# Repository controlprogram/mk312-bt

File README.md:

MK-312BT V1.2

Documentation at : http://tinyurl.com/mk312bt-info

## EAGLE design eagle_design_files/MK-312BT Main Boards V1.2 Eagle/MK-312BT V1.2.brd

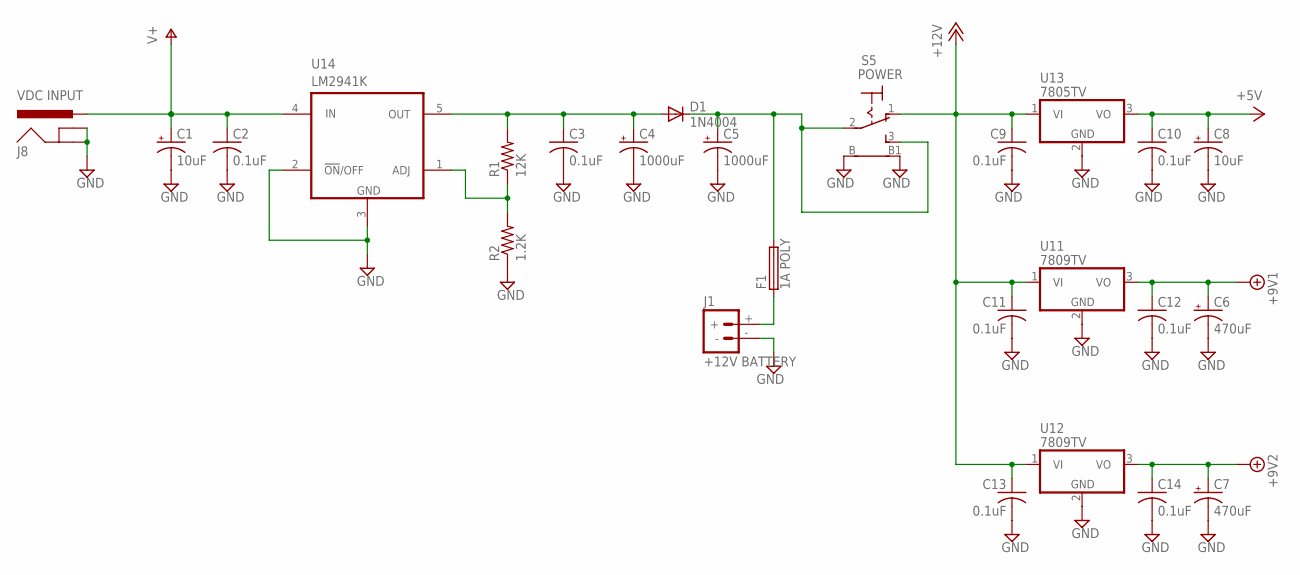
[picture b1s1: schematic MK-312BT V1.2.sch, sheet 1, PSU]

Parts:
C1, C8: 10uF; E2,5-7
C2, C3, C9, C10, C11, C12, C13, C14: 0.1uF; C025-024X044
C4, C5: 1000uF; E5-10,5
C6, C7: 470uF; E3,5-8
D1: 1N4004; DO41-10
F1: 1A POLY; LITTLEFUSE
J1: +12V BATTERY; DEANS
J8: VDC INPUT; POWER_JACK_SLOT
R1: 12K; 0207/10
R2: 1.2K; 0207/10
S5: POWER; LPV-1
U11, U12: 7809TV; TO220V
U13: 7805TV; TO220V
U14: LM2941K; TO220-5KC

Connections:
+5V: C8.+, C10.1, U13.3 (VO); also elsewhere on the board
+8V: C6.+, C12.1, U11.3 (VO); also elsewhere on the board
+9V: C7.+, C14.1, U12.3 (VO); also elsewhere on the board
+12V: C9.1, C11.1, C13.1, S5.1 (O), U11.1 (VI), U12.1 (VI), U13.1 (VI); also elsewhere on the board
GND: C1.-, C2.2, C3.2, C4.-, C5.-, C6.-, C7.-, C8.-, C9.2, C10.2, C11.2, C12.2, C13.2, C14.2, J1.-, J8.GND@1 (GNDBREAK), J8.GND@2 (GND), R2.1, S5.B, S5.B1, U11.2 (GND), U12.2 (GND), U13.2 (GND), U14.2 (!ON!/OFF), U14.3 (GND); also elsewhere on the board
unnamed: F1.1, J1.+
unnamed: R1.1, R2.2, U14.1 (ADJ)
unnamed: C3.1, C4.+, D1.A, R1.2, U14.5 (OUT)
unnamed: C5.+, D1.C, F1.2, S5.2, S5.3 (S)
V+: C1.+, C2.1, J8.PWR, U14.4 (IN); also elsewhere on the board

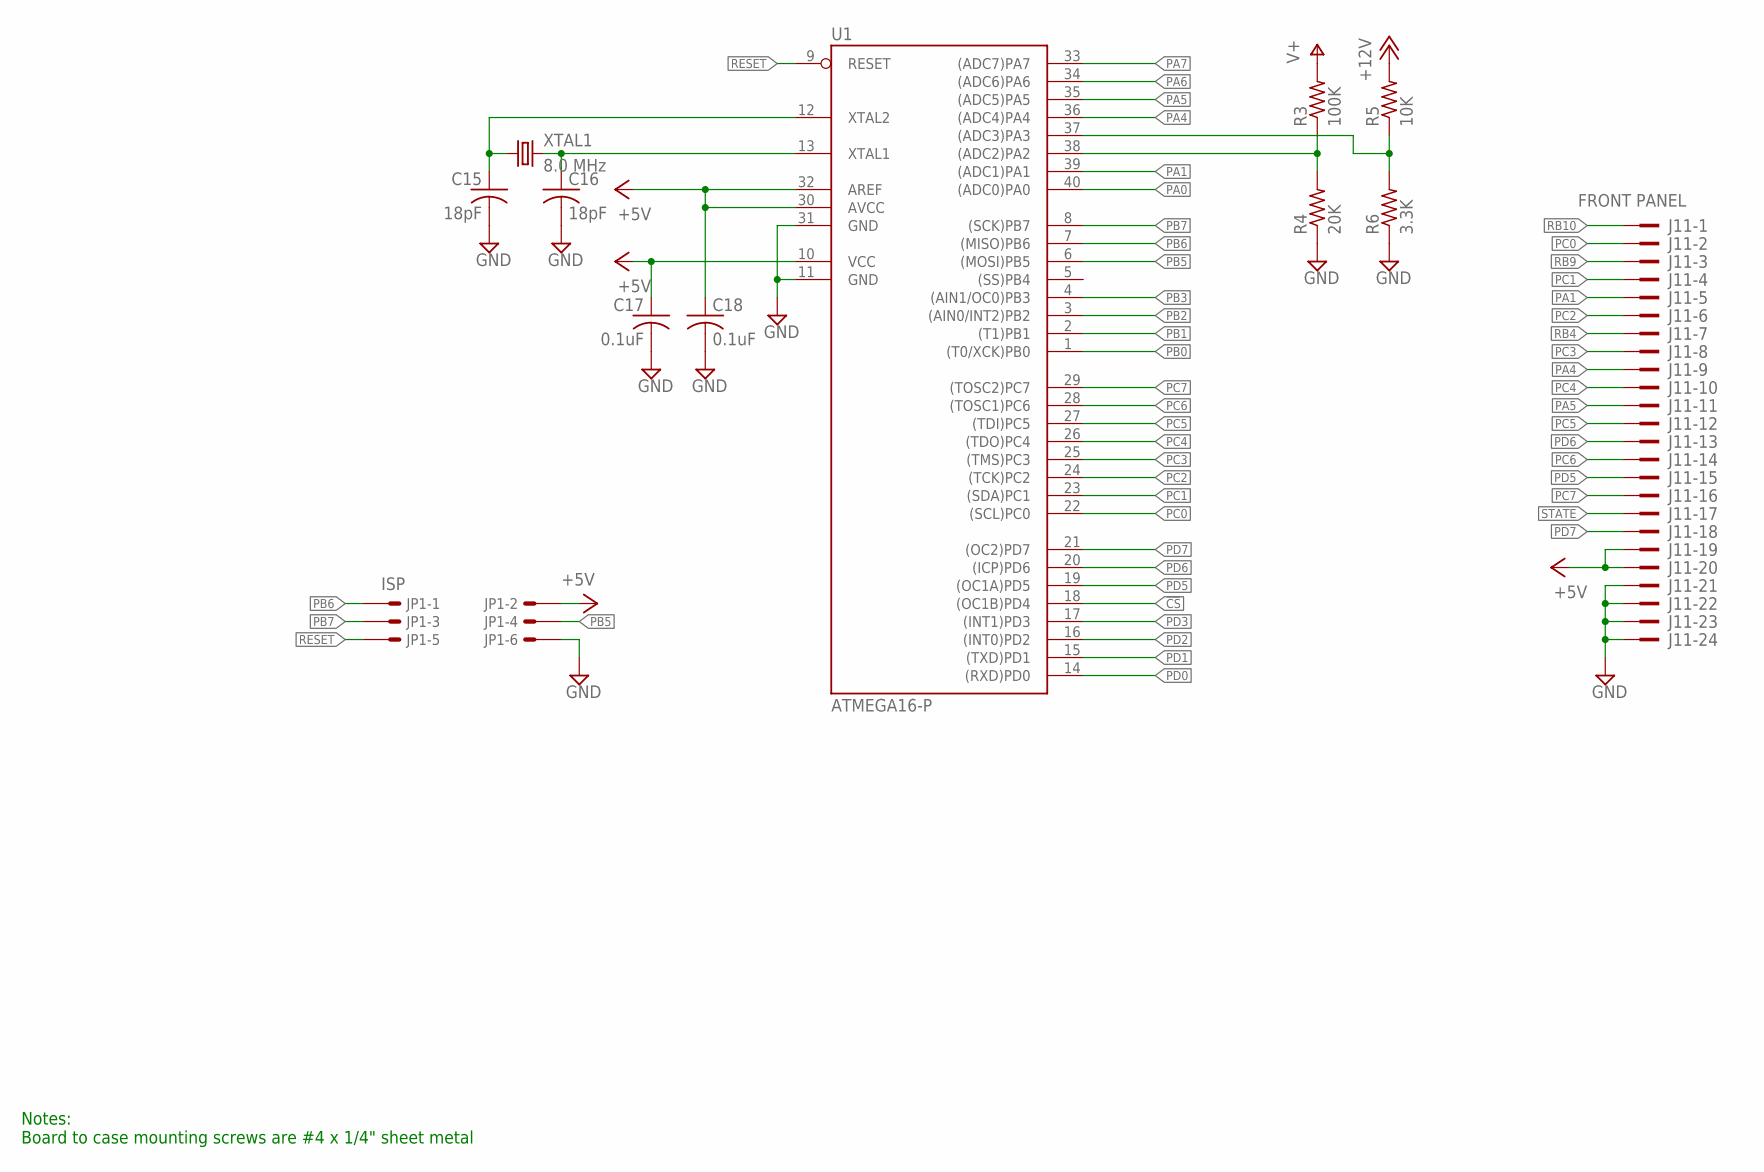
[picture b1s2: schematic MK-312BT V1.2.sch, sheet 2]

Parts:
C15, C16: 18pF; C025-024X044
C17, C18: 0.1uF; C025-024X044
J11: FRONT PANEL; PAK100/2500-24
JP1: ISP; 057-006-1
R3: 100K; 0207/10
R4: 20K; 0207/10
R5: 10K; 0207/10
R6: 3.3K; 0207/10
U1: ATMEGA16-P; DIL40
XTAL1: 8.0 MHz; HC49/S

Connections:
!CS: U1.18 ((OC1B)PD4); also elsewhere on the board
+5V: C17.1, C18.1, J11.19, J11.20, JP1.2, U1.10 (VCC), U1.30 (AVCC), U1.32 (AREF); also elsewhere on the board
+12V: R5.2; also elsewhere on the board
GND: C15.2, C16.2, C17.2, C18.2, J11.21, J11.22, J11.23, J11.24, JP1.6, R4.1, R6.1, U1.11 (GND), U1.31 (GND); also elsewhere on the board
unnamed: R5.1, R6.2, U1.37 ((ADC3)PA3)
unnamed: R3.1, R4.2, U1.38 ((ADC2)PA2)
unnamed: C16.1, U1.13 (XTAL1), XTAL1.2
unnamed: C15.1, U1.12 (XTAL2), XTAL1.1
PA0: U1.40 ((ADC0)PA0); also elsewhere on the board
PA1: J11.5, U1.39 ((ADC1)PA1); also elsewhere on the board
PA4: J11.9, U1.36 ((ADC4)PA4)
PA5: J11.11, U1.35 ((ADC5)PA5)
PA6: U1.34 ((ADC6)PA6); also elsewhere on the board
PA7: U1.33 ((ADC7)PA7); also elsewhere on the board
PB0: U1.1 ((T0/XCK)PB0); also elsewhere on the board
PB1: U1.2 ((T1)PB1); also elsewhere on the board
PB2: U1.3 ((AIN0/INT2)PB2); also elsewhere on the board
PB3: U1.4 ((AIN1/OC0)PB3); also elsewhere on the board
PB5: JP1.4, U1.6 ((MOSI)PB5); also elsewhere on the board
PB6: JP1.1, U1.7 ((MISO)PB6)
PB7: JP1.3, U1.8 ((SCK)PB7); also elsewhere on the board
PC0: J11.2, U1.22 ((SCL)PC0); also elsewhere on the board
PC1: J11.4, U1.23 ((SDA)PC1); also elsewhere on the board
PC2: J11.6, U1.24 ((TCK)PC2); also elsewhere on the board
PC3: J11.8, U1.25 ((TMS)PC3); also elsewhere on the board
PC4: J11.10, U1.26 ((TDO)PC4); also elsewhere on the board
PC5: J11.12, U1.27 ((TDI)PC5); also elsewhere on the board
PC6: J11.14, U1.28 ((TOSC1)PC6); also elsewhere on the board
PC7: J11.16, U1.29 ((TOSC2)PC7); also elsewhere on the board
PD0: U1.14 ((RXD)PD0); also elsewhere on the board
PD1: U1.15 ((TXD)PD1); also elsewhere on the board
PD2: U1.16 ((INT0)PD2); also elsewhere on the board
PD3: U1.17 ((INT1)PD3); also elsewhere on the board
PD5: J11.15, U1.19 ((OC1A)PD5); also elsewhere on the board
PD6: J11.13, U1.20 ((ICP)PD6); also elsewhere on the board
PD7: J11.18, U1.21 ((OC2)PD7); also elsewhere on the board
RB4: J11.7; also elsewhere on the board
RB9: J11.3; also elsewhere on the board
RB10: J11.1; also elsewhere on the board
RESET: JP1.5, U1.9 (RESET)
STATE: J11.17; also elsewhere on the board
V+: R3.2; also elsewhere on the board

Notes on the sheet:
Notes: Board to case mounting screws are #4 x 1/4" sheet metal

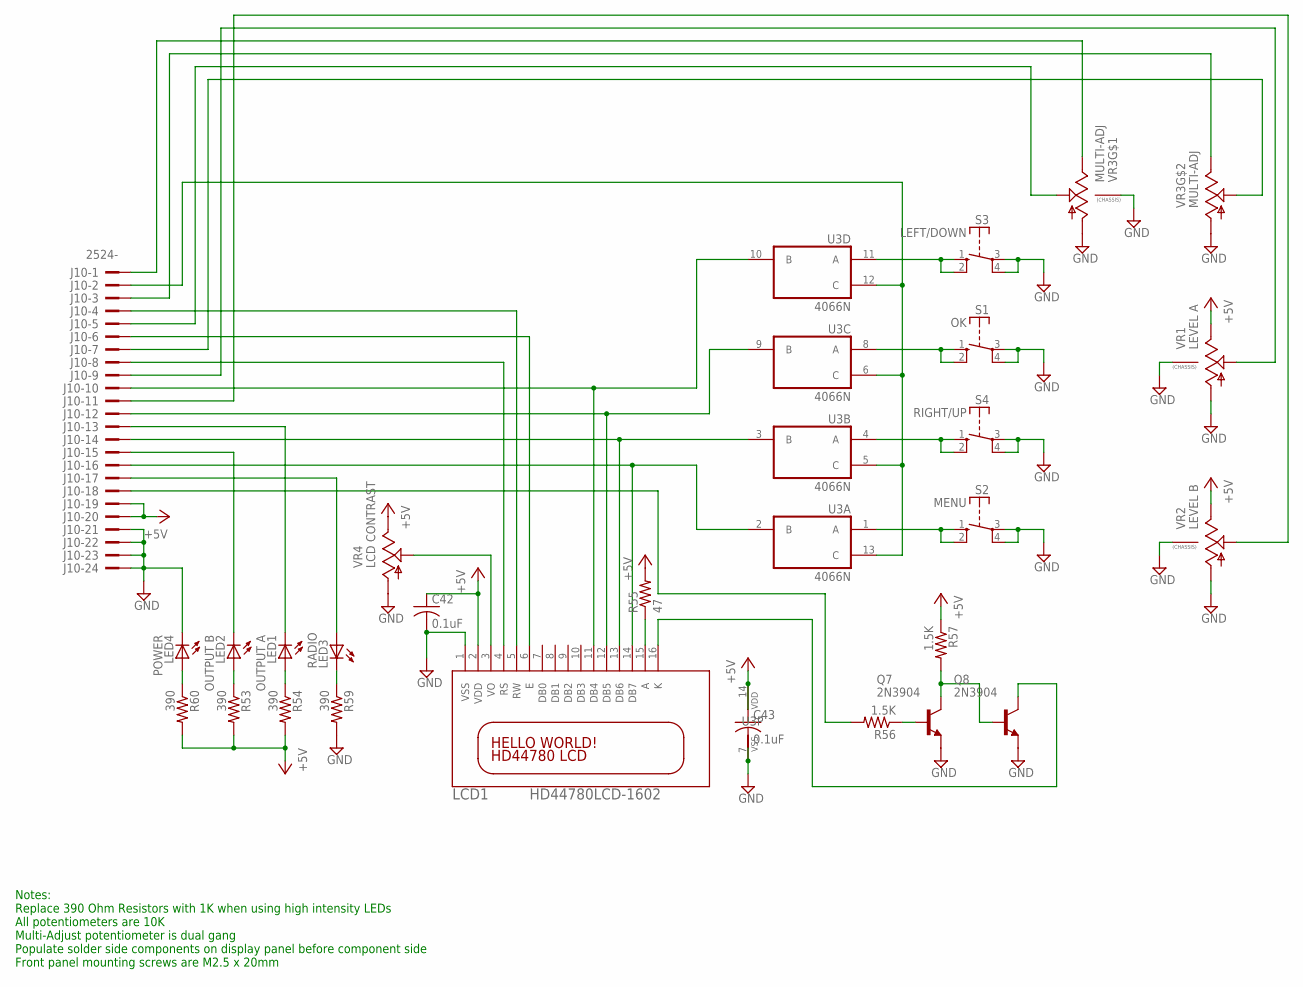
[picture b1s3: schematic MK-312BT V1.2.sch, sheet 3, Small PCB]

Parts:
C42, C43: 0.1uF; C025-024X044
J10: 2524-; PAK100/2500-24
LCD1: HD44780LCD-1602; LCD1602
LED1: OUTPUT A; LED5MM
LED2: OUTPUT B; LED5MM
LED3: RADIO; LED5MM
LED4: POWER; LED5MM
Q7, Q8: 2N3904; TO92
R53, R54, R59, R60: 390; 0207/10
R55: 47; 0207/10
R56, R57: 1.5K; 0207/10
S1: OK; DTE6K
S2: MENU; DTE6K
S3: LEFT/DOWN; DTE6K
S4: RIGHT/UP; DTE6K
U3: 4066N; DIL14
VR1: LEVEL A; 9MM_SNAP-IN_POT
VR2: LEVEL B; 9MM_SNAP-IN_POT
VR3: MULTI-ADJ; DUAL_9MM_SNAP-IN_POT
VR4: LCD CONTRAST; B25P

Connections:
+5V: C42.1, C43.1, J10.19, J10.20, LCD1.2 (VDD), R53.2, R54.2, R55.2, R57.1, R60.2, U3.14 (VDD), VR1.3 (E), VR2.3 (E), VR4.E; also elsewhere on the board
GND: C42.2, C43.2, J10.21, J10.22, J10.23, J10.24, LCD1.1 (VSS), LED4.K (C), Q7.3 (E), Q8.3 (E), R59.2, S1.3, S1.4, S2.3, S2.4, S3.3, S3.4, S4.3, S4.4, U3.7 (VSS), VR1.1 (A), VR1.CHASSIS2, VR2.1 (A), VR2.CHASSIS2, VR3.1 (A), VR3.1B (A), VR3.CHASSIS1, VR3.CHASSIS2, VR4.A; also elsewhere on the board
unnamed: J10.7, VR3.2B (S)
unnamed: S1.1 (S), S1.2 (S), U3.8 (A)
unnamed: S3.1 (S), S3.2 (S), U3.11 (A)
unnamed: S4.1 (S), S4.2 (S), U3.4 (A)
unnamed: J10.3, VR3.3B (E)
unnamed: J10.9, VR1.2 (S)
unnamed: J10.11, VR2.2 (S)
unnamed: J10.1, VR3.3 (E)
unnamed: J10.5, VR3.2 (S)
unnamed: LED2.A, R53.1
unnamed: LED1.A, R54.1
unnamed: LCD1.3 (VO), VR4.S
unnamed: LCD1.15 (A), R55.1
unnamed: LED3.K (C), R59.1
unnamed: S2.1 (S), S2.2 (S), U3.1 (A)
unnamed: LED4.A, R60.1
unnamed: Q7.2 (B), R56.1
unnamed: Q7.1 (C), Q8.2 (B), R57.2
unnamed: LCD1.16 (K), Q8.1 (C)
unnamed: J10.17, LED3.A
PC0: J10.2, U3.5 (C), U3.6 (C), U3.12 (C), U3.13 (C); also elsewhere on the board
PC1: J10.4, LCD1.5 (RW); also elsewhere on the board
PC2: J10.6, LCD1.6 (E); also elsewhere on the board
PC3: J10.8, LCD1.4 (RS); also elsewhere on the board
PC4: J10.10, LCD1.11 (DB4), U3.10 (B); also elsewhere on the board
PC5: J10.12, LCD1.12 (DB5), U3.9 (B); also elsewhere on the board
PC6: J10.14, LCD1.13 (DB6), U3.3 (B); also elsewhere on the board
PC7: J10.16, LCD1.14 (DB7), U3.2 (B); also elsewhere on the board
PD5: J10.15, LED2.K (C); also elsewhere on the board
PD6: J10.13, LED1.K (C); also elsewhere on the board
PD7: J10.18, R56.2; also elsewhere on the board

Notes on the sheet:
Notes: Replace 390 Ohm Resistors with 1K when using high intensity LEDs All potentiometers are 10K Multi-Adjust potentiometer is dual gang Populate solder side components on display panel before component side Front panel mounting screws are M2.5 x 20mm

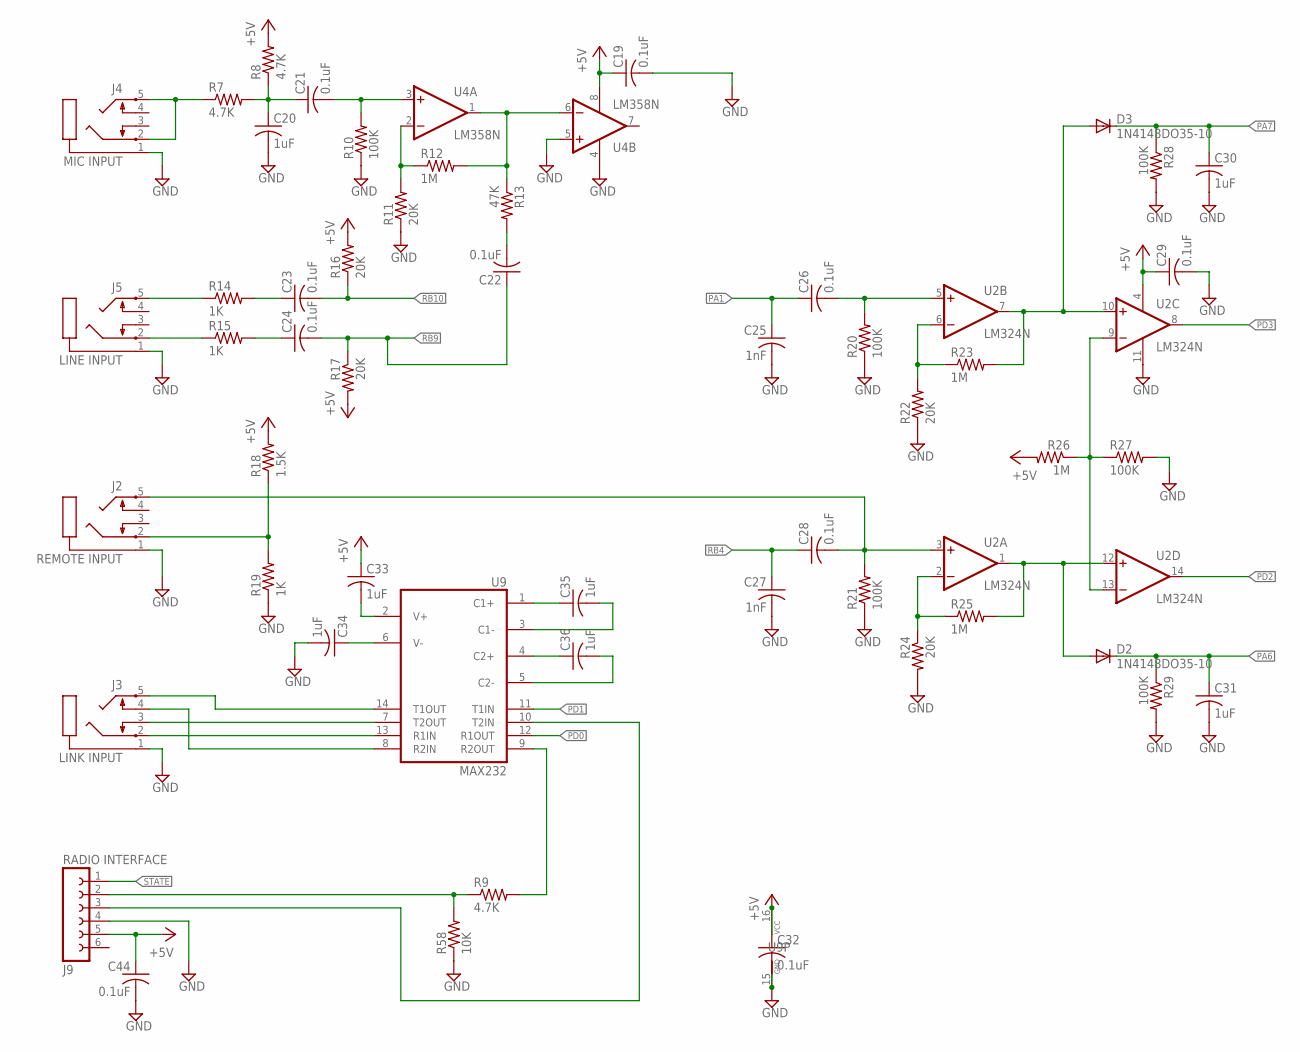
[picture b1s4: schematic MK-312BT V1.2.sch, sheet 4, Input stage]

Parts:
C19, C21, C22, C23, C24, C26, C28, C29, C32, C44: 0.1uF; C025-024X044
C20, C30, C31, C33, C34, C35, C36: 1uF; C025-024X044
C25, C27: 1nF; C025-024X044
D2, D3: 1N4148DO35-10; DO35-10
J2: REMOTE INPUT; STX3100
J3: LINK INPUT; STX3100
J4: MIC INPUT; STX3100
J5: LINE INPUT; STX3100
J9: RADIO INTERFACE; FE06
R7, R8, R9: 4.7K; 0207/10
R10, R20, R21, R27, R28, R29: 100K; 0207/10
R11, R16, R17, R22, R24: 20K; 0207/10
R12, R23, R25, R26: 1M; 0207/10
R13: 47K; 0207/10
R14, R15, R19: 1K; 0207/10
R18: 1.5K; 0207/10
R58: 10K; 0207/10
U2: LM324N; DIL14
U4: LM358N; DIL08
U9: MAX232; DIL16

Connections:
+5V: C19.1, C29.1, C32.1, C33.1, C44.1, J9.5, R8.2, R16.2, R17.2, R18.2, R26.2, U2.4 (V+), U4.8 (V+), U9.16 (VCC); also elsewhere on the board
GND: C19.2, C20.2, C25.2, C27.2, C29.2, C30.2, C31.2, C32.2, C34.2, C44.2, J2.1, J3.1, J4.1, J5.1, J9.4, R10.1, R11.1, R19.1, R20.1, R21.1, R22.1, R24.2, R27.2, R28.2, R29.2, R58.1, U2.11 (V-), U4.4 (V-), U4.5 (+IN), U9.15 (GND); also elsewhere on the board
unnamed: C28.2, J2.5, R21.2, U2.3 (+IN)
unnamed: R9.2, U9.9 (R2OUT)
unnamed: J3.5, U9.14 (T1OUT)
unnamed: J3.2, U9.13 (R1IN)
unnamed: C35.1, U9.1 (C1+)
unnamed: R24.1, R25.1, U2.2 (-IN)
unnamed: D2.A, R25.2, U2.1 (OUT), U2.12 (+IN)
unnamed: J5.2, R15.1
unnamed: J5.5, R14.1
unnamed: C23.1, R14.2
unnamed: J2.2, R18.1, R19.2
unnamed: R22.2, R23.1, U2.6 (-IN)
unnamed: C35.2, U9.3 (C1-)
unnamed: R26.1, R27.1, U2.9 (-IN), U2.13 (-IN)
unnamed: C26.2, R20.2, U2.5 (+IN)
unnamed: C24.1, R15.2
unnamed: C36.2, U9.5 (C2-)
unnamed: C36.1, U9.4 (C2+)
unnamed: J9.2, R9.1, R58.2
unnamed: D3.A, R23.2, U2.7 (OUT), U2.10 (+IN)
unnamed: C34.1, U9.6 (V-)
unnamed: J4.2, J4.5, R7.1
unnamed: C20.1, C21.1, R7.2, R8.1
unnamed: C21.2, R10.2, U4.3 (+IN)
unnamed: R11.2, R12.1, U4.2 (-IN)
unnamed: R12.2, R13.1, U4.1 (OUT), U4.6 (-IN)
unnamed: C22.2, R13.2
unnamed: C33.2, U9.2 (V+)
unnamed: J3.4, U9.8 (R2IN)
unnamed: J3.3, U9.7 (T2OUT)
unnamed: J9.3, U9.10 (T2IN)
PA1: C25.1, C26.1; also elsewhere on the board
PA6: C31.1, D2.C, R29.1; also elsewhere on the board
PA7: C30.1, D3.C, R28.1; also elsewhere on the board
PD0: U9.12 (R1OUT); also elsewhere on the board
PD1: U9.11 (T1IN); also elsewhere on the board
PD2: U2.14 (OUT); also elsewhere on the board
PD3: U2.8 (OUT); also elsewhere on the board
RB4: C27.1, C28.1; also elsewhere on the board
RB9: C22.1, C24.2, R17.1; also elsewhere on the board
RB10: C23.2, R16.1; also elsewhere on the board
STATE: J9.1; also elsewhere on the board

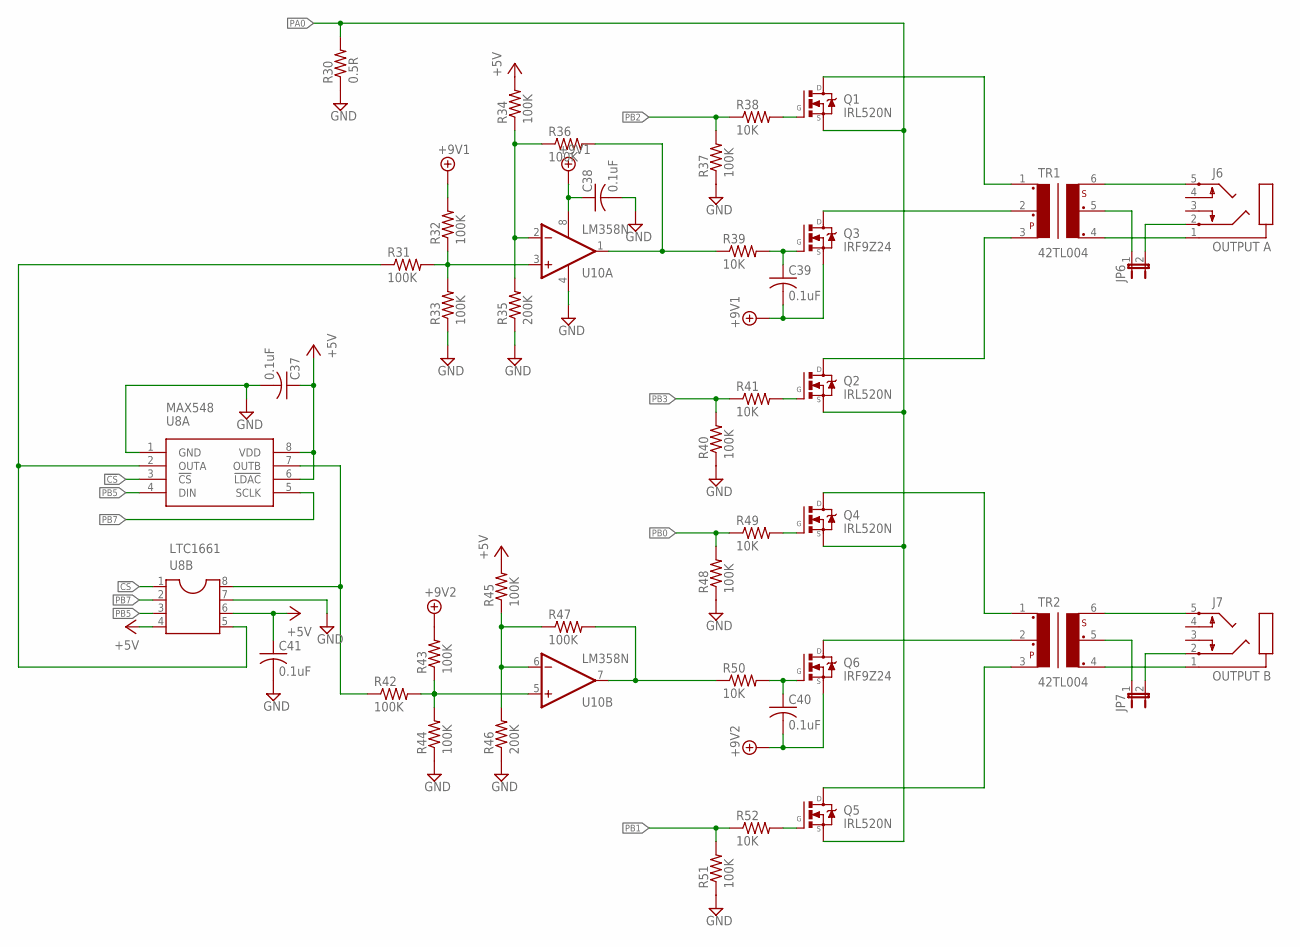
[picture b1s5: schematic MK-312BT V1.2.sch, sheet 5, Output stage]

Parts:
C37, C38, C39, C40, C41: 0.1uF; C025-024X044
J6: OUTPUT A; STX3100
J7: OUTPUT B; STX3100
JP6, JP7: JP1E; JP1
Q1, Q2, Q4, Q5: IRL520N; TO220V
Q3, Q6: IRF9Z24; TO220V
R30: 0.5R; 0309/12
R31, R32, R33, R34, R36, R37, R40, R42, R43, R44, R45, R47, R48, R51: 100K; 0207/10
R35, R46: 200K; 0207/10
R38, R39, R41, R49, R50, R52: 10K; 0207/10
TR1, TR2: 42TL004; 42TL
U8A: MAX548; DIL08
U8B: LTC1661; SOCKET-08
U10: LM358N; DIL08

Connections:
!CS: U8A.3 (!CS), U8B.1; also elsewhere on the board
+5V: C37.1, C41.1, R34.2, R45.2, U8A.6 (!LDAC), U8A.8 (VDD), U8B.4, U8B.6; also elsewhere on the board
+8V: C38.1, C39.2, Q3.3 (S), R32.2, U10.8 (V+); also elsewhere on the board
+9V: C40.2, Q6.3 (S), R43.2; also elsewhere on the board
GND: C37.2, C38.2, C41.2, R30.1, R33.1, R35.1, R37.1, R40.1, R44.1, R46.1, R48.1, R51.1, U8A.1 (GND), U8B.7, U10.4 (V-); also elsewhere on the board
unnamed: J6.1, TR1.4
unnamed: JP7.1, TR2.5
unnamed: J6.5, TR1.6
unnamed: Q1.1 (G), R38.2
unnamed: Q2.1 (G), R41.2
unnamed: J7.2, JP7.2
unnamed: C39.1, Q3.1 (G), R39.2
unnamed: R31.2, R32.1, R33.2, U10.3 (+IN)
unnamed: Q4.1 (G), R49.2
unnamed: Q5.1 (G), R52.2
unnamed: C40.1, Q6.1 (G), R50.2
unnamed: R42.2, R43.1, R44.2, U10.5 (+IN)
unnamed: Q1.2 (D), TR1.1
unnamed: Q3.2 (D), TR1.2
unnamed: Q4.2 (D), TR2.1
unnamed: Q6.2 (D), TR2.2
unnamed: Q5.2 (D), TR2.3
unnamed: Q2.2 (D), TR1.3
unnamed: R34.1, R35.2, R36.1, U10.2 (-IN)
unnamed: R45.1, R46.2, R47.1, U10.6 (-IN)
unnamed: R31.1, U8A.2 (OUTA), U8B.5
unnamed: J6.2, JP6.2
unnamed: J7.5, TR2.6
unnamed: J7.1, TR2.4
unnamed: JP6.1, TR1.5
unnamed: R42.1, U8A.7 (OUTB), U8B.8
PA0: Q1.3 (S), Q2.3 (S), Q4.3 (S), Q5.3 (S), R30.2; also elsewhere on the board
PB0: R48.2, R49.1; also elsewhere on the board
PB1: R51.2, R52.1; also elsewhere on the board
PB2: R37.2, R38.1; also elsewhere on the board
PB3: R40.2, R41.1; also elsewhere on the board
PB5: U8A.4 (DIN), U8B.3; also elsewhere on the board
PB7: U8A.5 (SCLK), U8B.2; also elsewhere on the board
PFET_A: R36.2, R39.1, U10.1 (OUT)
PFET_B: R47.2, R50.1, U10.7 (OUT)

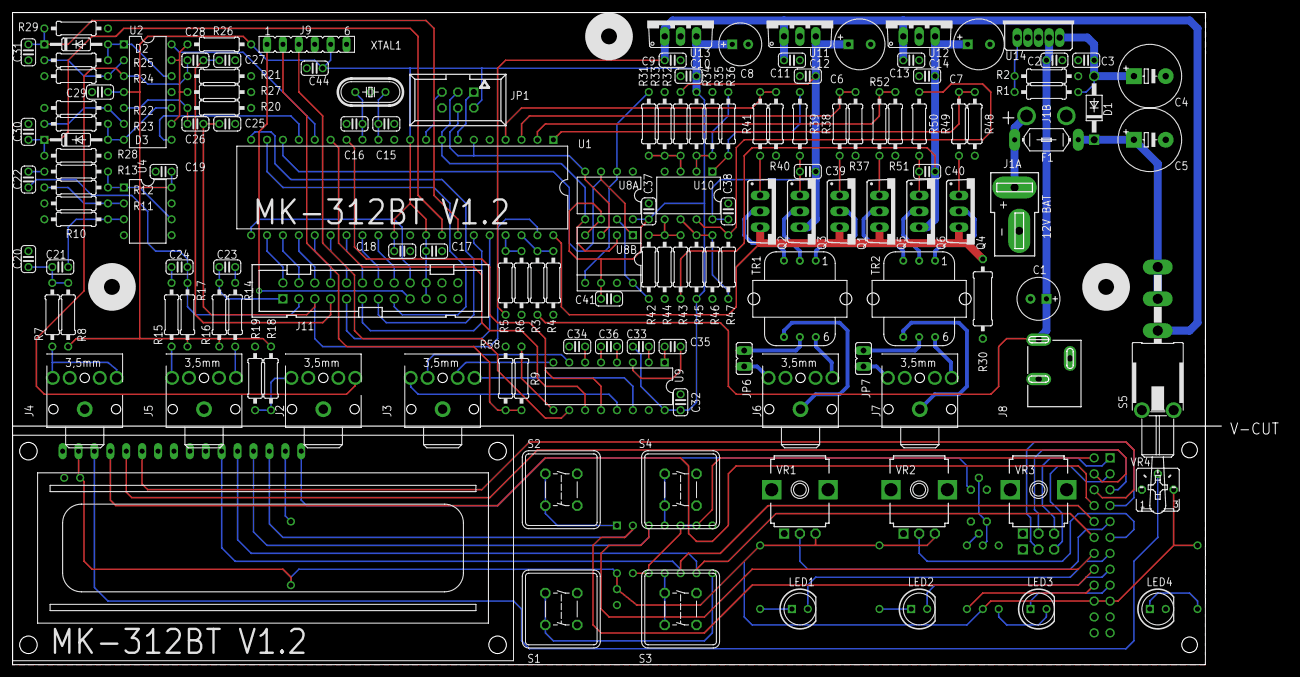
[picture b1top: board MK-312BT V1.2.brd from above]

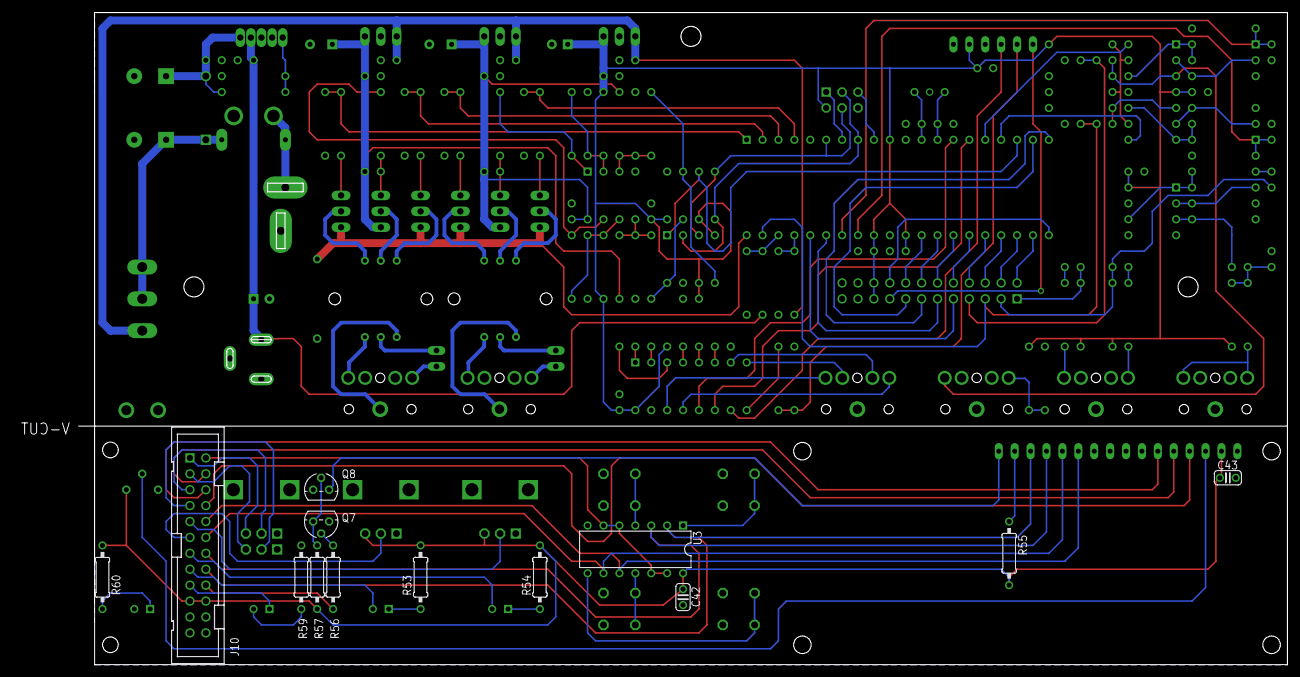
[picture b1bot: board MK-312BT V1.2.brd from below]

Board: 2 copper layers, 193.0 x 104.1 mm, 159 parts (13 on the bottom side), 127 nets.

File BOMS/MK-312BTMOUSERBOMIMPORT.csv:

Designator,Description,Quantity per Unit,Supplier,Supplier Part Number,Mfg Part Number,Alternate Part
R55,RES 47R,1,Mouser,660-MF1/4DC47R0F,MF1/4DC47R0F,
"R53,R54,R59,R60",RES 390R,4,Mouser,660-MF1/4DCT52R3900F,MF1/4DCT52R3900F,
"C10,C11,C12,C13,C14,C17,C18,C19,C2,C21,C22,C23,C24,C26,C28,C29,C3,C32,C37,C38,C39,C40,C41,C42,C43,C44,C9","CAP 0.1uF (0.1"" spacing) 50V",27,Mouser,80-C320C104K5R,C320C104K5R5TA,
R30,RES 0.5R 1/2W,1,Mouser,660-CF1/2CT52RR50J,CF1/2CT52RR50J,
R2,RES 1.2K,1,Mouser,660-MF1/4DCT52R1201F,MF1/4DCT52R1201F,
"R18, R56,R57",RES 1.5K,3,Mouser,660-MF1/4DCT52R1501F,MF1/4DCT52R1501F,
"C4,C5",1000uF 16V minimum,2,Mouser,647-UPW1E102MPD6,UPW1E102MPD6,
"R10,R20,R21,R27,R28,R29,R3,R31,R32,R33,R34,R36,R37,R40,R42,R43,R44,R45,R47,R48,R51",RES 100K,21,Mouser,660-MF1/4DC1003F,MF1/4DC1003F,
"R38,R39,R41,R49,R5,R50,R52,R58",RES 10K,8,Mouser,660-MF1/4DC1002F,MF1/4DC1002F,660-MF1/4DCT52R1002F
C8,CAP 10uF,1,Mouser,647-USV1H100MFD1TP,USV1H100MFD1TP,
C1,CAP 10uF CER,1,Mouser,810-FG11X7R1H106KRT6,FG11X7R1H106KRT06,
R1A,RES 12K,1,Mouser,660-MF1/4DCT52R1202F,MF1/4DCT52R1202F,
"C15,C16",CAP 18pF,2,Mouser,80-C315C180J1G,C315C180J1G5TA,
F1,1A POLYFUSE,1,Mouser,650-LVR100S,LVR100S,
"R14,R15,R19,",RES 1K,3,Mouser,660-MF1/4DCT52R1001F,MF1/4DCT52R1001F,
"R12,R23,R25,R26",RES 1M,4,Mouser,660-MF1/4DCT52R1004F,MF1/4DCT52R1004F,
D1,DIODE 1N4004,1,Mouser,621-1N4004,1N4004-T,
"D2,D3",DIODE 1N4148,2,Mouser,512-1N4148,1N4148,
"C25,C27","CAP 1nF (0.1"" spacing)",2,Mouser,80-C315C102K1G,C315C102K1G5TA,
"C20,C30,C31,C33,C34,C35,C36","CAP 1uF (0.1"" spacing)",7,Mouser,80-C315C105K3R,C315C105K3R5TA,
"R35,R46",RES 200K,2,Mouser,660-MF1/4DCT52R2003F,MF1/4DCT52R2003F,
"R11,R16,R17,R22,R24,R4",RES 20K,6,Mouser,660-MF1/4DCT52R2002F,MF1/4DCT52R2002F,
"J10,J11",PAK100/2500-24 - 2425-  3M WALL HEADER,2,Mouser,517-N2524-6002RB,N2524-6002RB,
"Q7,Q8",TRANS. 2N3904,2,Mouser,512-2N3904BU,2N3904BU,
R6,RES 3.3K,1,Mouser,660-MF1/4DCT52R3301F,MF1/4DCT52R3301F,
"R7,R8,R9",RES 4.7K,3,Mouser,660-MF1/4DCT52R4701F,MF1/4DCT52R4701F,
U3,CD4066N,1,Mouser,595-CD4066BE,CD4066BE,
"TR1,TR2",42TL004,2,Mouser,42TL004-RC,42TL004-RC,
"C6,C7",CAP 470uF 16V,2,Mouser,647-UHE1E471MPD,UHE1E471MPD,
R13,RES 47K,1,Mouser,660-MF1/4DCT52R4702F,MF1/4DCT52R4702F,
U13,VREG 7805T,1,Mouser,511-L7805CV,L7805CV,511-L7805ACP
"U11,U12",VREG 7809TV,2,Mouser,511-L7809CV,L7809CV,
XTAL1,8MHZ XTAL HC-49S ,1,Mouser,717-9B-8.000MEEJ-B,9B-8.000MEEJ-B,
U1,ATMEGA 16P,1,Mouser,556-ATMEGA16A-PU,ATMEGA16A-PU,556-ATMEGA16L-8PU                 ELSE SEE DIGIKEY ON NONMOUSER
LCD1,LCD HD44780LCD-1602,1,Mouser,763-0216K1Z-NSW-BBW,NHD-0216K1Z-NSW-FBW-L,763-0216K1Z-NSW-FBW
"Q3,Q6",MOSFET IRF9Z24,2,Mouser,942-IRF9Z24NPBF,IRF9Z24NPBF,
"Q1,Q2,Q4,Q5",MOSFET IRL520N,4,Mouser,942-IRL520NPBF,IRL520NPBF,
JP1,ISP 6 PIN,1,Mouser,571-5-146254-3,5-146254-3,
U14,LM2941,1,Mouser,926-LM2941CT/NOPB,LM2941CT/NOPB,
U2,LM324N,1,Mouser,595-LM324NE3,LM324NE3,595-LM324N
"U10,U4",LM358N,2,Mouser,512-LM358N,LM358N,
U8A,MAX548 (For V1.5 and below firmware) suggest using LTC1661 purchased from Digikey (see end of sheet),0,Mouser,700-MAX548ACPA,MAX548ACPA+,
"LED1,LED2,LED3,LED4",5MM LED,4,Mouser,606-4304H1,4304H1,
U9,MAX232,1,Mouser,700-MAX232CPE,MAX232CPE,
"SOCKET FOR U2,U3",DIL 14 IC SOCKET,2,Mouser,517-4814-3004-CP,4814-3004-CP,
SOCKET FOR U9,DIL 16 IC SOCKET,1,Mouser,517-4816-3004-CP,4816-3004-CP,
SOCKET FOR U1,DIL 40 IC SOCKET,1,Mouser,575-11041640410010,110-41-640-41-001000,
"SOCKET FOR U10,U4,U8(A/B)",DIL 8 IC SOCKET,4,Mouser,571-1-2199298-2,1-2199298-2,
"JP6,JP7",2x1 SIP HEADER 0.1,2,Mouser,571-5-146285-2,5-146285-2,
"VR1, VR2",ALPS 9mm 10K Pot,2,Mouser,688-RK09L1140A2U,RK09L1140A2U,
VR3,ALPS 9mm 10K Dual Gang Pot,1,Mouser,688-RK09L1240A12,RK09L1240A12,
VR4,Bourns 3362P 10K Pot,1,Mouser,3362P-1-103LF,3362P-1-103LF,
"S1,S2,S3,S4",Buttons,4,Mouser,611-D6C90F2LFS,D6C90 F2 LFS,
"J2,J3,J4,J5,J6,J7",3.5mm stereo jack,6,Mouser,806-STX-3100-5NB,STX-3100-5NB,
J8,2.1/5.5mm DC jack,1,Mouser,490-PJ-002A,PJ-002A,
S5,Toggle Switch with safety actuator,1,Mouser,611-7101K2AV2BE,7101K2AV2BE,611-7101K2AV2QE
J9,Radio Header,1,Mouser,538-90147-1206,90147-1206,
Gray button covers,Button Cover,2,Mouser,611-BTND610F,BTND610F,611-BTND690F
White button covers,Button Cover,2,Mouser,611-BTND600F,BTN D6 00 F,
LCD HEADER,LCD Header,1,Mouser,710-61301611121,61301611121,
Knob,Potentiometer Knob,3,Mouser,450-BA761,BA761,
BAT1,Lead Acid Battery,1,Mouser,547-PS-1220,PS-1220,
BAT1 Lugs,Crimp Lubs for BAT1,2,Mouser,534-8291,534-8291,
Power Supply,"18V, 1A .5.5mm OD plug",1,Mouser,709-GST18U18-P1J,GST18U18-P1J,709-GST25U15-P1J

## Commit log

2017-02-11 Initial commit, v1.2 of mk312-bt board
2017-02-23 Added v1.2 updates, pictures, bluetooth config tool/docs
2017-06-04 Rename directories to make windows happy
    Fixes #2

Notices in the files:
parts and their libraries:
SparkFun-Connectors: Licensing: Creative Commons ShareAlike 4.0 International - https://creativecommons.org/licenses/by-sa/4.0
national-semi: Copyright (C) 2008, Bob Starr
